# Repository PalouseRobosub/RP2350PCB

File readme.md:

## Rp2350 PCB
PCB for using the Rp2350 over CAN, exposing GPIO and ADC pins, designed in KiCAD v9

Current revision is a prototype for verifying we can actually hand assemble all the parts, hence the use of a linear regulator and dense size for optimizing cost.
Next revision will likely be bigger and use a switching regulator.

Designed for OshPark design rules at https://docs.oshpark.com/design-tools/kicad/kicad-design-rules/

Please refer to Library/LibraryReference.md for component attribution

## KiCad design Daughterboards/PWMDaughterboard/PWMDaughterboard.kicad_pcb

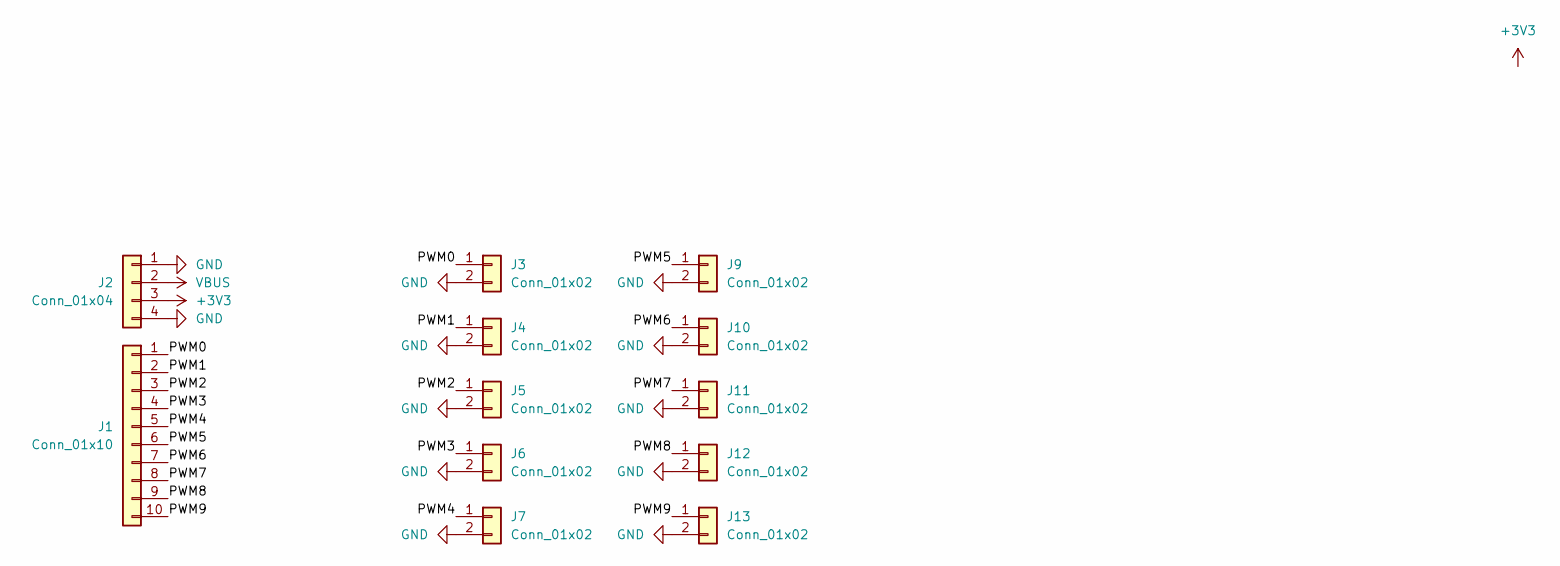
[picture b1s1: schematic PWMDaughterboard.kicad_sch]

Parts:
J1: Conn_01x10; PinHeader_1x10_P2.00mm_Vertical_SMD_Pin1Left
J2: Conn_01x04; PinHeader_1x04_P2.00mm_Vertical_SMD_Pin1Left
J3, J4, J5, J6, J7, J9, J10, J11, J12, J13: Conn_01x02; JST_GH_BM02B-GHS-TBT_1x02-1MP_P1.25mm_Vertical

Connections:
+3V3: J2.3
/PWM0: J1.1, J3.1
/PWM1: J1.2, J4.1
/PWM2: J1.3, J5.1
/PWM3: J1.4, J6.1
/PWM4: J1.5, J7.1
/PWM5: J1.6, J9.1
/PWM6: J1.7, J10.1
/PWM7: J1.8, J11.1
/PWM8: J1.9, J12.1
/PWM9: J1.10, J13.1
GND: J2.1, J2.4, J3.2, J4.2, J5.2, J6.2, J7.2, J9.2, J10.2, J11.2, J12.2, J13.2
VBUS: J2.2

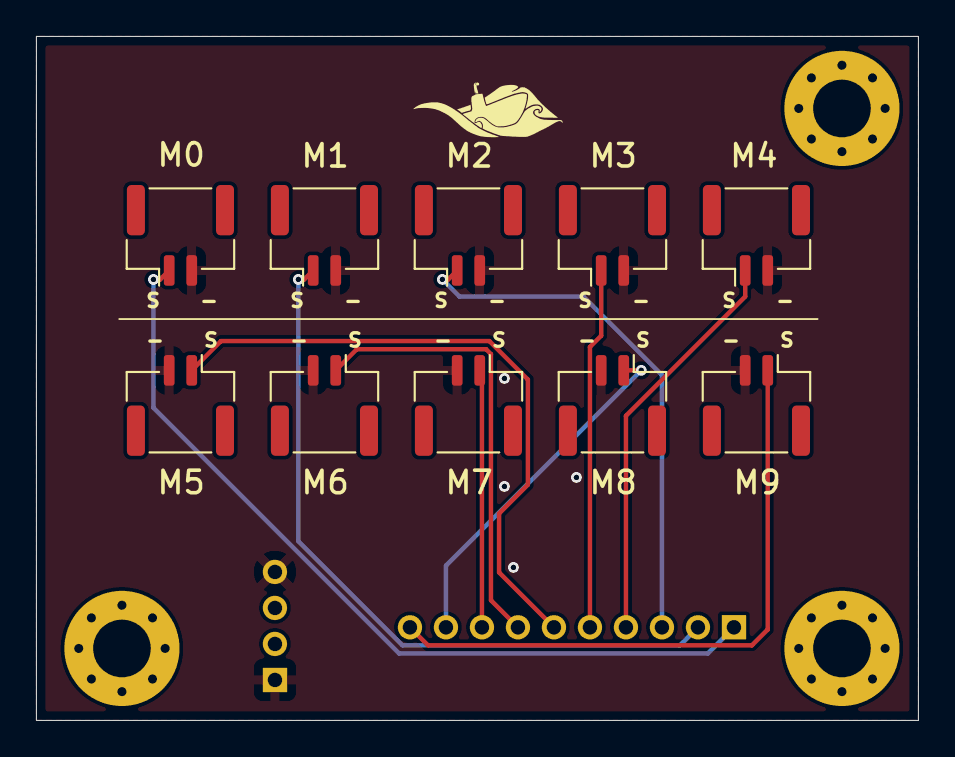
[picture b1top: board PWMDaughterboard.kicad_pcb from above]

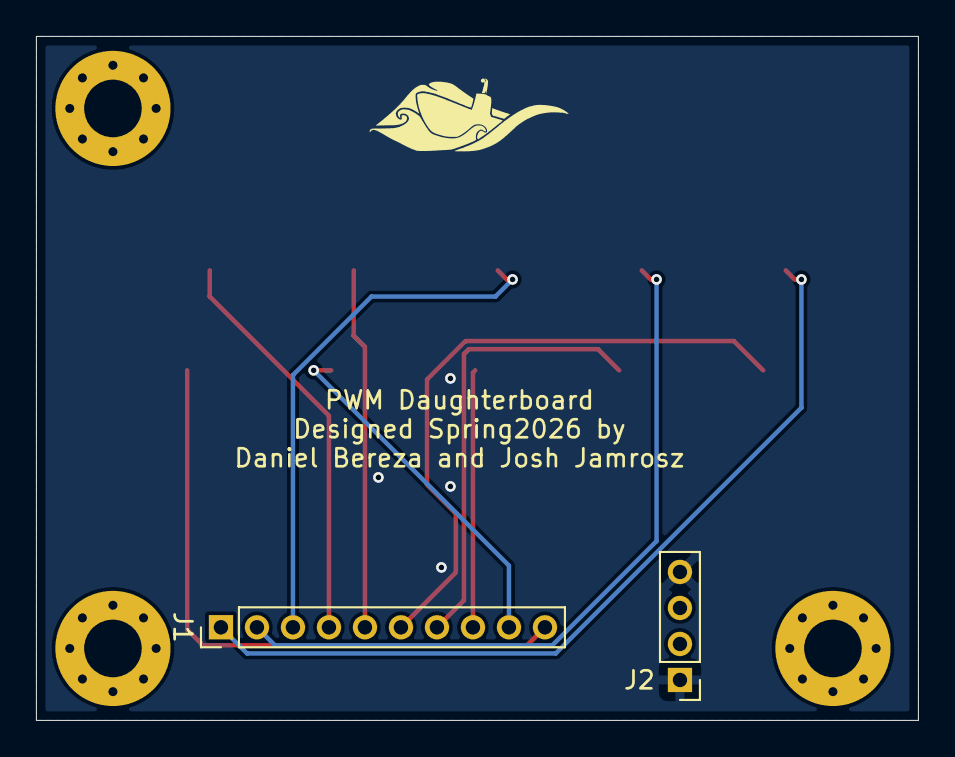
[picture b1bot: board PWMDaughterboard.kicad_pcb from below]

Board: 2 copper layers, 49.0 x 38.0 mm, 12 parts (2 on the bottom side), 11 nets.

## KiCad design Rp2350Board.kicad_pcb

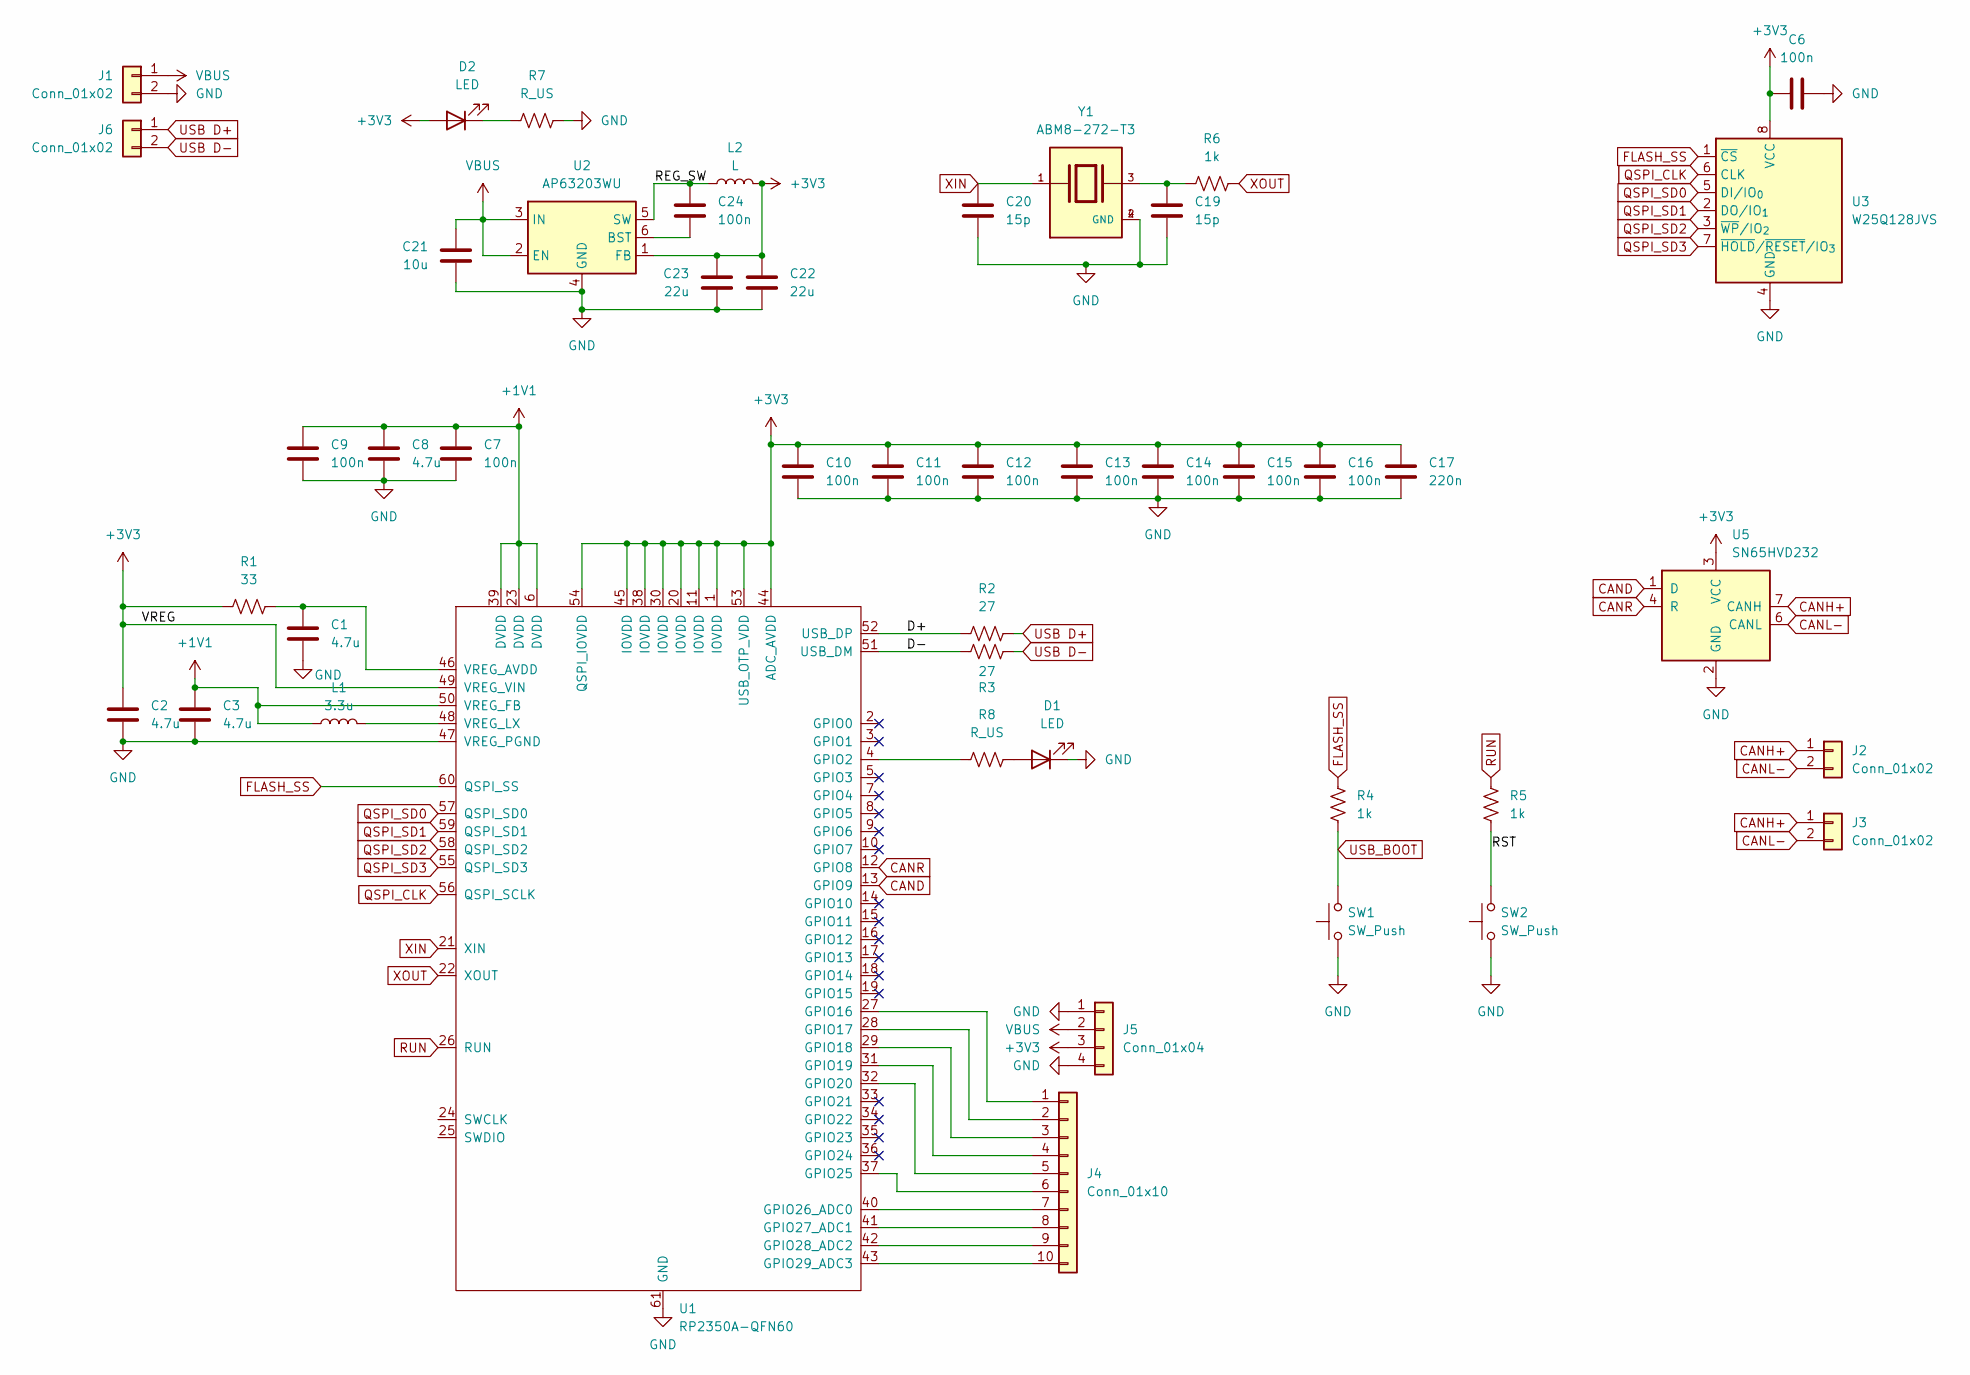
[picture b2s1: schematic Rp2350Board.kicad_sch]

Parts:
C1, C2, C3, C8: 4.7u; C_0603_1608Metric
C6, C7, C9, C10, C11, C12, C13, C14, C15, C16, C24: 100n; C_0603_1608Metric
C17: 220n; C_0603_1608Metric
C19, C20: 15p; C_0603_1608Metric
C21: 10u; C_0603_1608Metric
C22, C23: 22u; C_0603_1608Metric
D1, D2: LED; LED_0603_1608Metric
J1, J2, J3, J6: Conn_01x02; JST_GH_SM02B-GHS-TB_1x02-1MP_P1.25mm_Horizontal
J4: Conn_01x10; PinSocket_1x10_P2.00mm_Vertical_SMD_Pin1Left
J5: Conn_01x04; PinSocket_1x04_P2.00mm_Vertical_SMD_Pin1Left
L1: 3.3u; AOTAB201610S3R3101T
L2: L; PA5430
R1: 33; R_0603_1608Metric
R2, R3: 27; R_0603_1608Metric
R4, R5, R6: 1k; R_0603_1608Metric
R7, R8: R_US; R_0603_1608Metric
SW1, SW2: SW_Push; SW_EVQ-P7A01P
U1: RP2350A-QFN60; RP2350A_QFN-60_EP_7.75x7.75_Pitch0.4mm
U2: AP63203WU; TSOT-23-6
U3: W25Q128JVS; SOIC-8_5.3x5.3mm_P1.27mm
U5: SN65HVD232; SOIC-8_3.9x4.9mm_P1.27mm
Y1: ABM8-272-T3; XTAL_ABM8-272-T3; PARTREV 07-29-20

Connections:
+1V1: C3.1, C7.1, C8.1, C9.1, L1.1, U1.6 (DVDD), U1.23 (DVDD), U1.39 (DVDD), U1.50 (VREG_FB)
+3V3: C2.1, C6.2, C10.1, C11.1, C12.1, C13.1, C14.1, C15.1, C16.1, C17.1, C22.2, C23.1, D2.2 (A), J5.3, L2.2, R1.1, U1.1 (IOVDD), U1.11 (IOVDD), U1.20 (IOVDD), U1.30 (IOVDD), U1.38 (IOVDD), U1.44 (ADC_AVDD), U1.45 (IOVDD), U1.49 (VREG_VIN), U1.53 (USB_OTP_VDD), U1.54 (QSPI_IOVDD), U2.1 (FB), U3.8 (VCC), U5.3 (VCC)
/D+: R2.1, U1.52 (USB_DP)
/D-: R3.1, U1.51 (USB_DM)
/REG_SW: C24.1, L2.1, U2.5 (SW)
/RST: R5.1, SW2.2_1 (2)
CAND: U1.13 (GPIO9), U5.1 (D)
CANH+: J2.1, J3.1, U5.7 (CANH)
CANL-: J2.2, J3.2, U5.6 (CANL)
CANR: U1.12 (GPIO8), U5.4 (R)
FLASH_SS: R4.1, U1.60 (QSPI_SS), U3.1 (~CS)
GND: C1.2, C2.2, C3.2, C6.1, C7.2, C8.2, C9.2, C10.2, C11.2, C12.2, C13.2, C14.2, C15.2, C16.2, C17.2, C19.2, C20.2, C21.2, C22.1, C23.2, D1.1 (K), J1.2, J5.1, J5.4, R7.2, SW1.1_1, SW2.1_1, U1.47 (VREG_PGND), U1.61 (GND), U2.4 (GND), U3.4 (GND), U5.2 (GND), Y1.2 (GND), Y1.4 (GND)
unnamed: C19.1, R6.1, Y1.3
unnamed: D1.2 (A), R8.2
unnamed: D2.1 (K), R7.1
unnamed: J4.1, U1.27 (GPIO16)
unnamed: J4.2, U1.28 (GPIO17)
unnamed: J4.3, U1.29 (GPIO18)
unnamed: J4.4, U1.31 (GPIO19)
unnamed: J4.5, U1.32 (GPIO20)
unnamed: J4.6, U1.37 (GPIO25)
unnamed: J4.7, U1.40 (GPIO26_ADC0)
unnamed: J4.8, U1.41 (GPIO27_ADC1)
unnamed: J4.9, U1.42 (GPIO28_ADC2)
unnamed: J4.10, U1.43 (GPIO29_ADC3)
unnamed: R8.1, U1.4 (GPIO2)
unnamed: C1.1, R1.2, U1.46 (VREG_AVDD)
unnamed: L1.2, U1.48 (VREG_LX)
unnamed: C24.2, U2.6 (BST)
QSPI_CLK: U1.56 (QSPI_SCLK), U3.6 (CLK)
QSPI_SD0: U1.57 (QSPI_SD0), U3.5 (DI/IO_{0})
QSPI_SD1: U1.59 (QSPI_SD1), U3.2 (DO/IO_{1})
QSPI_SD2: U1.58 (QSPI_SD2), U3.3 (~WP/IO_{2})
QSPI_SD3: U1.55 (QSPI_SD3), U3.7 (~HOLD/~RESET/IO_{3})
RUN: R5.2, U1.26 (RUN)
USB D+: J6.1, R2.2
USB D-: J6.2, R3.2
USB_BOOT: R4.2, SW1.2_1 (2)
VBUS: C21.1, J1.1, J5.2, U2.2 (EN), U2.3 (IN)
XIN: C20.1, U1.21 (XIN), Y1.1
XOUT: R6.2, U1.22 (XOUT)

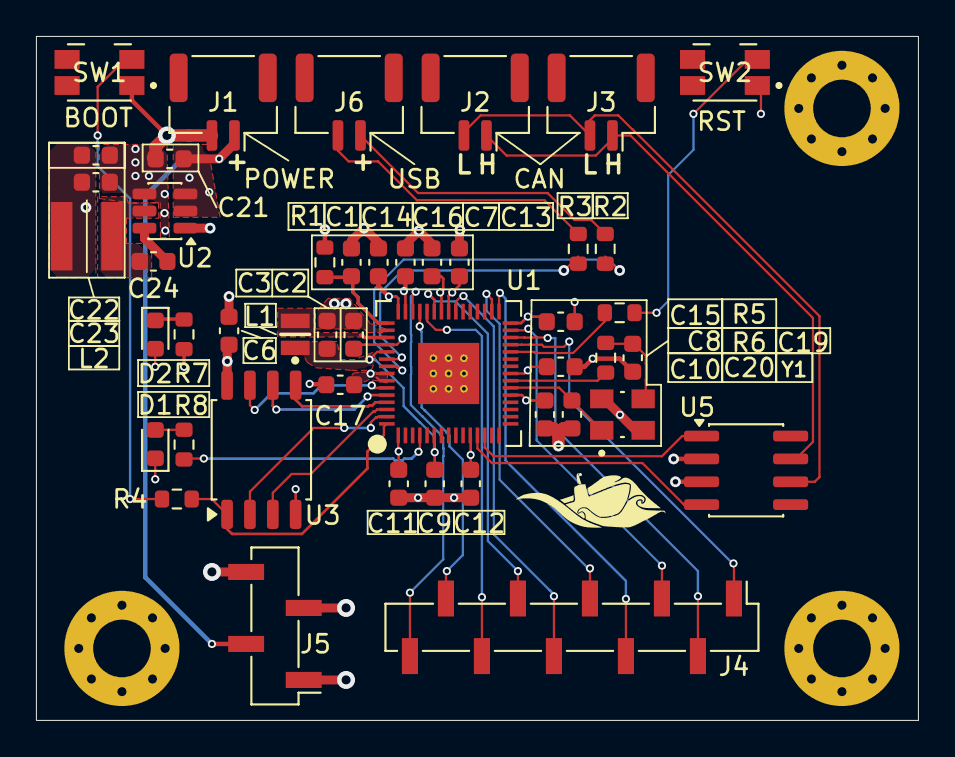
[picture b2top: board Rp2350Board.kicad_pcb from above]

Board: 4 copper layers, 49.0 x 38.0 mm, 46 parts (0 on the bottom side), 41 nets.

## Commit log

2026-01-16 Fix mislabel
2026-01-22 Added symbol, footprint, and model files for the PA5430
2026-01-22 First draft of v2 board
2026-01-22 Small edits to first draft of v2
2026-01-22 update AOTA inductor footprint
2026-01-22 Also fixed AOTA ind model
2026-01-22 and also fixed the model
2026-01-22 Remove locks
2026-01-22 Small fixups and cleanup of unused external library files
2026-02-09 Add PWM Daughterboard initial work
2026-02-10 Switched SMD headers J1,2 to through-hole
2026-02-10 cleaned up vias
2026-02-12 Added traces
2026-02-19 Added silkscreen
2026-02-19 Changed spacing
2026-02-19 Size adjustment
